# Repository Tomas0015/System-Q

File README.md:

# System-Q
System Q is an open source security system, based on the ESP microcontroller, with wireless and wired bus capabilities.
# I like cheese
We  hate cloud with a passion so there will not be a cloud integration developed by us, the most you will get is a GSM modem sending out SMS messages. 

 # Central control unit
-doesn't actually control anything, only contains a power supply and a battery.

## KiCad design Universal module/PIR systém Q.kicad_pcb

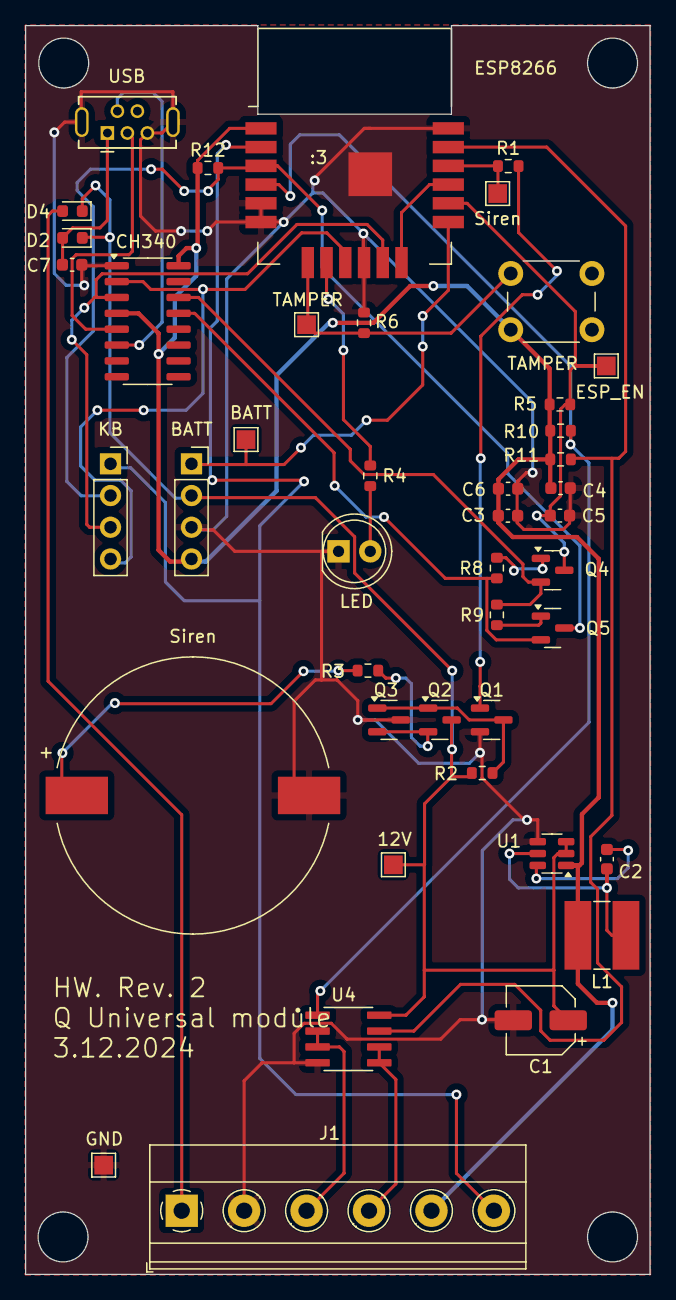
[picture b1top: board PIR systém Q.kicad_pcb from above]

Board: 2 copper layers, 50.0 x 100.0 mm, 43 parts (0 on the bottom side), 32 nets.

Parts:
12V: 12V; TestPoint_Pad_1.5x1.5mm
BATT: Conn_01x04_Socket; PinSocket_1x04_P2.54mm_Vertical
BATT#2: batt test; TestPoint_Pad_1.5x1.5mm
C1: 10u 50V; CP_Elec_5x5.3
C2, C5: 100n; C_0603_1608Metric
C3, C4: 22u; C_0603_1608Metric
C6, C7: 100nF; C_0603_1608Metric
CH340: CH340C; SOIC-16_3.9x9.9mm_P1.27mm
D2, D4: D; D_0603_1608Metric
ESP8266: WT8266-S1
ESP_EN: reset test; TestPoint_Pad_1.5x1.5mm
GND: GND; TestPoint_Pad_1.5x1.5mm
J1: Screw_Terminal_01x06; TerminalBlock_Phoenix_MKDS-1,5-6_1x06_P5.00mm_Horizontal
KB: Conn_01x04_Socket; PinSocket_1x04_P2.54mm_Vertical
L1: 4u7; L_Ferrocore_DLG-0504
LED: LED - R; LED_D5.0mm
Q1, Q2: BC846; SOT-23
Q3: BC857; SOT-23
Q4, Q5: BC817; SOT-23
R1, R2, R8, R9, R10, R11, R12: 10k; R_0603_1608Metric
R3: 820; R_0603_1608Metric
R4: 100R; R_0603_1608Metric
R5: 10K; R_0603_1608Metric
R6: 4k7; R_0603_1608Metric
Siren: buzzer test; TestPoint_Pad_1.5x1.5mm
Siren#2: Siren; LPT2270AS
TAMPER: tamper switch; SW_PUSH_6mm
TAMPER#2: tamper test; TestPoint_Pad_1.5x1.5mm
U1: AP63203WU; TSOT-23-6
U4: P82B96; SOIC127P599X175-8N
USB: USB_B_Mini; USB_Mini-B_Tensility_54-00023_Vertical

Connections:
+3.3V: BATT.4, C3.1, C4.1, C6.1, CH340.4 (V3), CH340.16 (VCC), ESP8266.1 (VCC), J1.5, L1.2, R5.2, R10.1, R11.1, R12.1, TAMPER.1 (A), U1.1 (FB)
+12V: 12V.1, BATT.2, C1.1, D2.1 (K), D4.1 (K), Q2.3 (C), R2.1, U1.2 (EN), U1.3 (IN), U4.8 (VCC)
ESP_EN: C5.1, ESP8266.14 (EN), ESP_EN.1, Q4.3 (C), R5.1
GND: BATT.3, C1.2, C3.2, C4.2, C5.2, C6.2, C7.2, CH340.1 (GND), ESP8266.5 (GPIO15), ESP8266.6 (GND), ESP8266.10 (GND), ESP8266.18 (GND), ESP8266.19, GND.1, J1.2, LED.1 (K), Q1.2 (E), Q3.3 (C), R6.2, Siren#2.2 (+), U1.4 (GND), U4.4 (GND), USB.5 (GND), USB.6 (Shield)
GPIO0: ESP8266.3 (GPIO0), KB.2, Q5.3 (C), R12.2
I2C data: ESP8266.4 (GPIO2), R10.2, U4.1 (SDA)
unnamed: R3.2, Siren#2.1 (-)
unnamed: LED.2 (A), R4.2
unnamed: C7.1, D2.2 (A), USB.1 (VBUS)
unnamed: D4.2 (A), J1.1
unnamed: CH340.5 (UD+), USB.3 (D+)
unnamed: CH340.6 (UD-), USB.2 (D-)
unnamed: Q1.1 (B), R1.2
unnamed: Q1.3 (C), Q2.1 (B), Q3.1 (B), R2.2
unnamed: Q2.2 (E), Q3.2 (E), R3.1
unnamed: Q4.1 (B), R8.2
unnamed: CH340.14 (~RTS), Q4.2 (E), R9.1
unnamed: Q5.1 (B), R9.2
unnamed: CH340.13 (~DTR), Q5.2 (E), R8.1
unnamed: C2.2, U1.6 (BST)
unnamed: C2.1, L1.1, U1.5 (SW)
unnamed: ESP8266.8 (GPIO5), R4.1
unnamed: ESP8266.12 (~RST), ESP8266.15 (GPIO16)
PIR Signal: ESP8266.2 (GPIO4), J1.6, KB.1
RX: CH340.2 (TXD), ESP8266.9 (GPIO3/RXD), KB.4
SCL: J1.4, U4.5 (TXD-SCL), U4.6 (RXD-SCL)
SDA: J1.3, U4.2 (RXD-SDA), U4.3 (TXD-SDA)
TX: CH340.3 (RXD), ESP8266.11 (GPIO1/TXD), KB.3
battery voltage: BATT.1, BATT#2.1, ESP8266.13 (ADC)
buzzer signal: ESP8266.16 (GPIO12), R1.1, Siren.1
clock: ESP8266.17 (GPIO14), R11.2, U4.7 (SCL)
tamper: ESP8266.7 (GPIO13), R6.1, TAMPER.2 (B), TAMPER#2.1

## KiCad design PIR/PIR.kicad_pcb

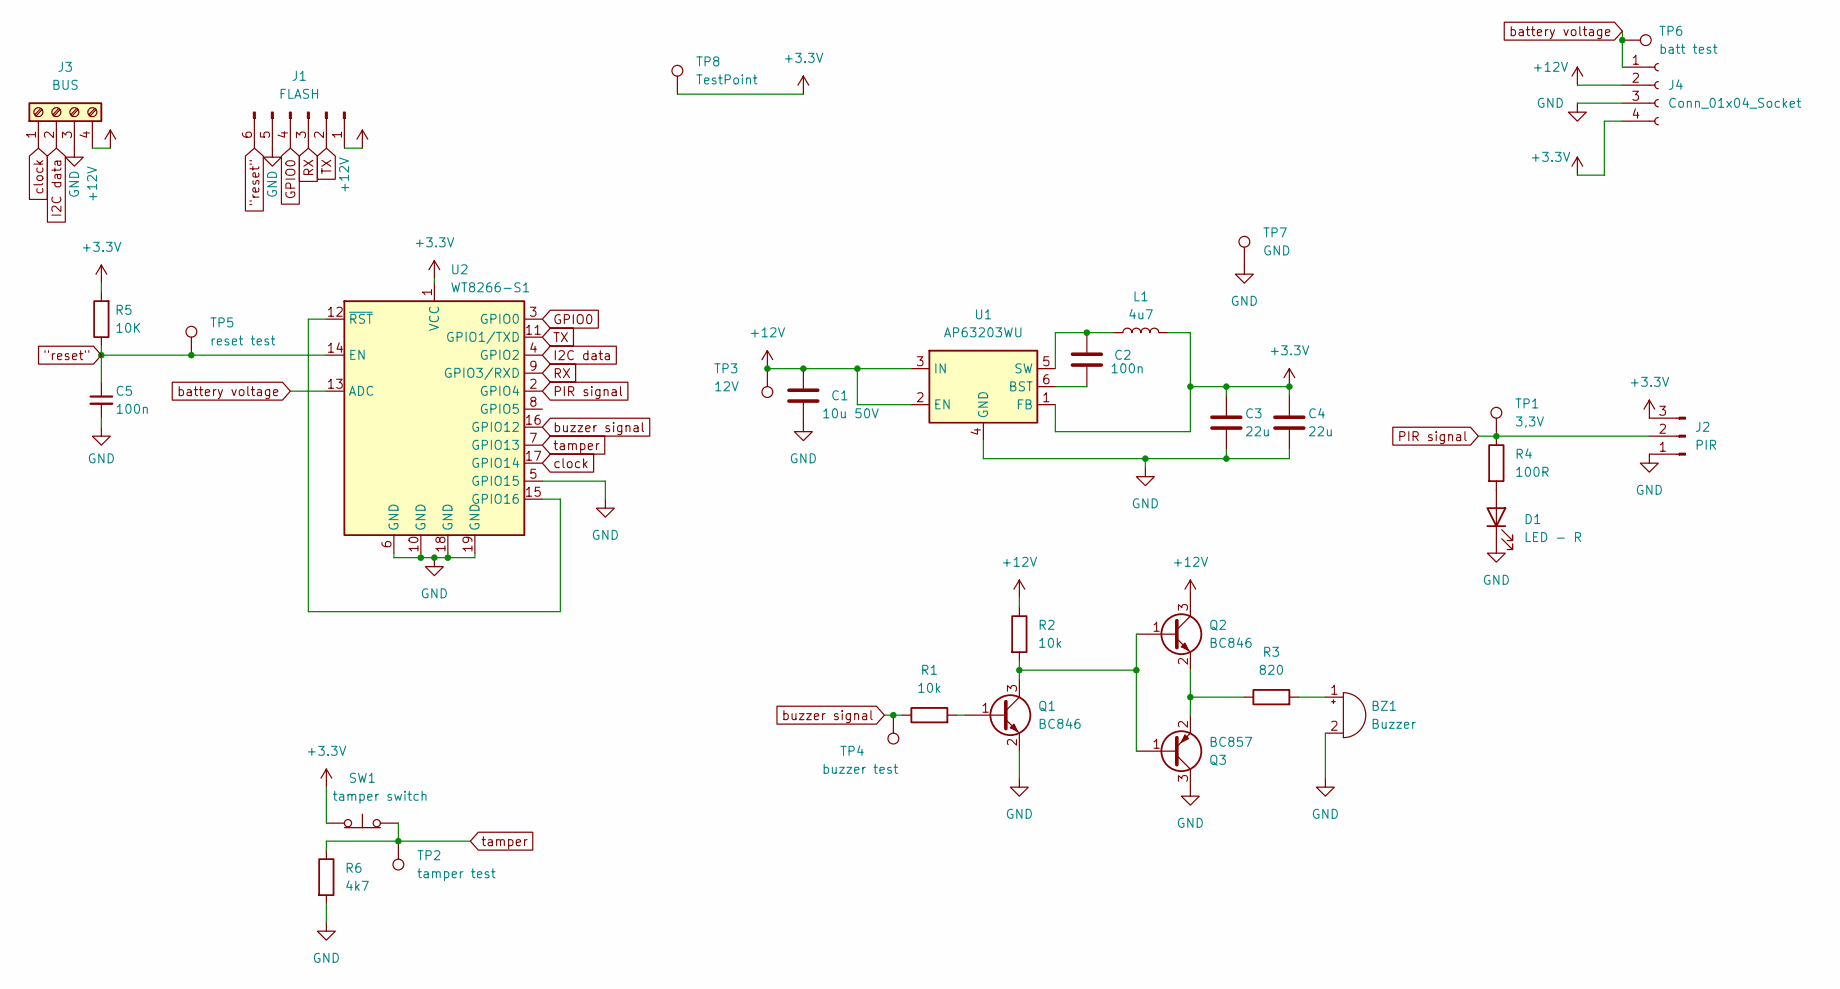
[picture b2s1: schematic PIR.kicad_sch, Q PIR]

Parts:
BZ1: Buzzer; LPT2270AS
C1: 10u 50V; CP_Elec_5x5.3
C2, C5: 100n; C_0603_1608Metric
C3, C4: 22u; C_0603_1608Metric
D1: LED - R; LED_D5.0mm
J1: FLASH; PinSocket_1x06_P2.54mm_Horizontal
J2: PIR; PinSocket_1x03_P2.54mm_Vertical
J3: BUS; TerminalBlock_Altech_AK300-4_P5.00mm
J4: Conn_01x04_Socket; PinSocket_1x04_P2.54mm_Horizontal
L1: 4u7; L_Ferrocore_DLG-0504
Q1, Q2: BC846; SOT-23
Q3: BC857; SOT-23
R1, R2: 10k; R_0603_1608Metric
R3: 820; R_0603_1608Metric
R4: 100R; R_0603_1608Metric
R5: 10K; R_0603_1608Metric
R6: 4k7; R_0603_1608Metric
SW1: tamper switch; SW_PUSH_6mm
TP1: 3,3V; TestPoint_Pad_1.5x1.5mm
TP2: tamper test; TestPoint_Pad_1.5x1.5mm
TP3: 12V; TestPoint_Pad_1.5x1.5mm
TP4: buzzer test; TestPoint_Pad_1.5x1.5mm
TP5: reset test; TestPoint_Pad_1.5x1.5mm
TP6: batt test; TestPoint_Pad_1.5x1.5mm
TP7: GND; TestPoint_Pad_1.5x1.5mm
TP8: TestPoint; TestPoint_Pad_1.5x1.5mm
U1: AP63203WU; TSOT-23-6
U2: WT8266-S1

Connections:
"reset": C5.1, J1.6, R5.1, TP5.1, U2.14 (EN)
+3.3V: C3.1, C4.1, J2.3, J4.4, L1.2, R5.2, SW1.1 (A), TP8.1, U1.1 (FB), U2.1 (VCC)
+12V: C1.1, J1.1, J3.4, J4.2, Q2.3 (C), R2.1, TP3.1, U1.2 (EN), U1.3 (IN)
GND: BZ1.2 (+), C1.2, C3.2, C4.2, C5.2, D1.1 (K), J1.5, J2.1, J3.3, J4.3, Q1.2 (E), Q3.3 (C), R6.2, TP7.1, U1.4 (GND), U2.5 (GPIO15), U2.6 (GND), U2.10 (GND), U2.18 (GND), U2.19 (GND)
GPIO0: J1.4, U2.3 (GPIO0)
I2C data: J3.2, U2.4 (GPIO2)
unnamed: BZ1.1 (-), R3.2
unnamed: D1.2 (A), R4.2
unnamed: Q1.1 (B), R1.2
unnamed: Q1.3 (C), Q2.1 (B), Q3.1 (B), R2.2
unnamed: Q2.2 (E), Q3.2 (E), R3.1
unnamed: C2.1, U1.6 (BST)
unnamed: C2.2, L1.1, U1.5 (SW)
unnamed: U2.12 (~RST), U2.15 (GPIO16)
PIR signal: J2.2, R4.1, TP1.1, U2.2 (GPIO4)
RX: J1.3, U2.9 (GPIO3/RXD)
TX: J1.2, U2.11 (GPIO1/TXD)
battery voltage: J4.1, TP6.1, U2.13 (ADC)
buzzer signal: R1.1, TP4.1, U2.16 (GPIO12)
clock: J3.1, U2.17 (GPIO14)
tamper: R6.1, SW1.2 (B), TP2.1, U2.7 (GPIO13)

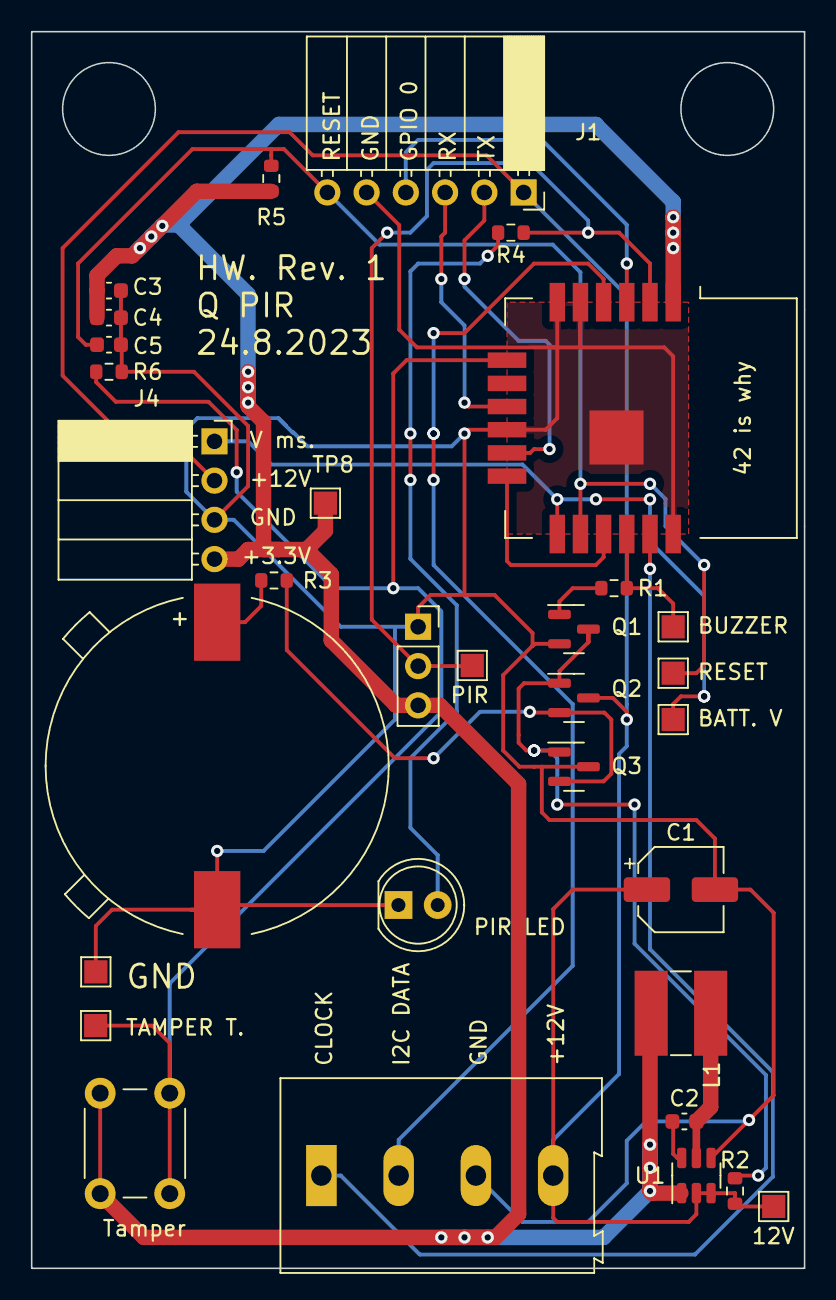
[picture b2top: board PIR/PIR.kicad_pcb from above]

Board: 2 copper layers, 50.0 x 80.0 mm, 32 parts (0 on the bottom side), 21 nets.

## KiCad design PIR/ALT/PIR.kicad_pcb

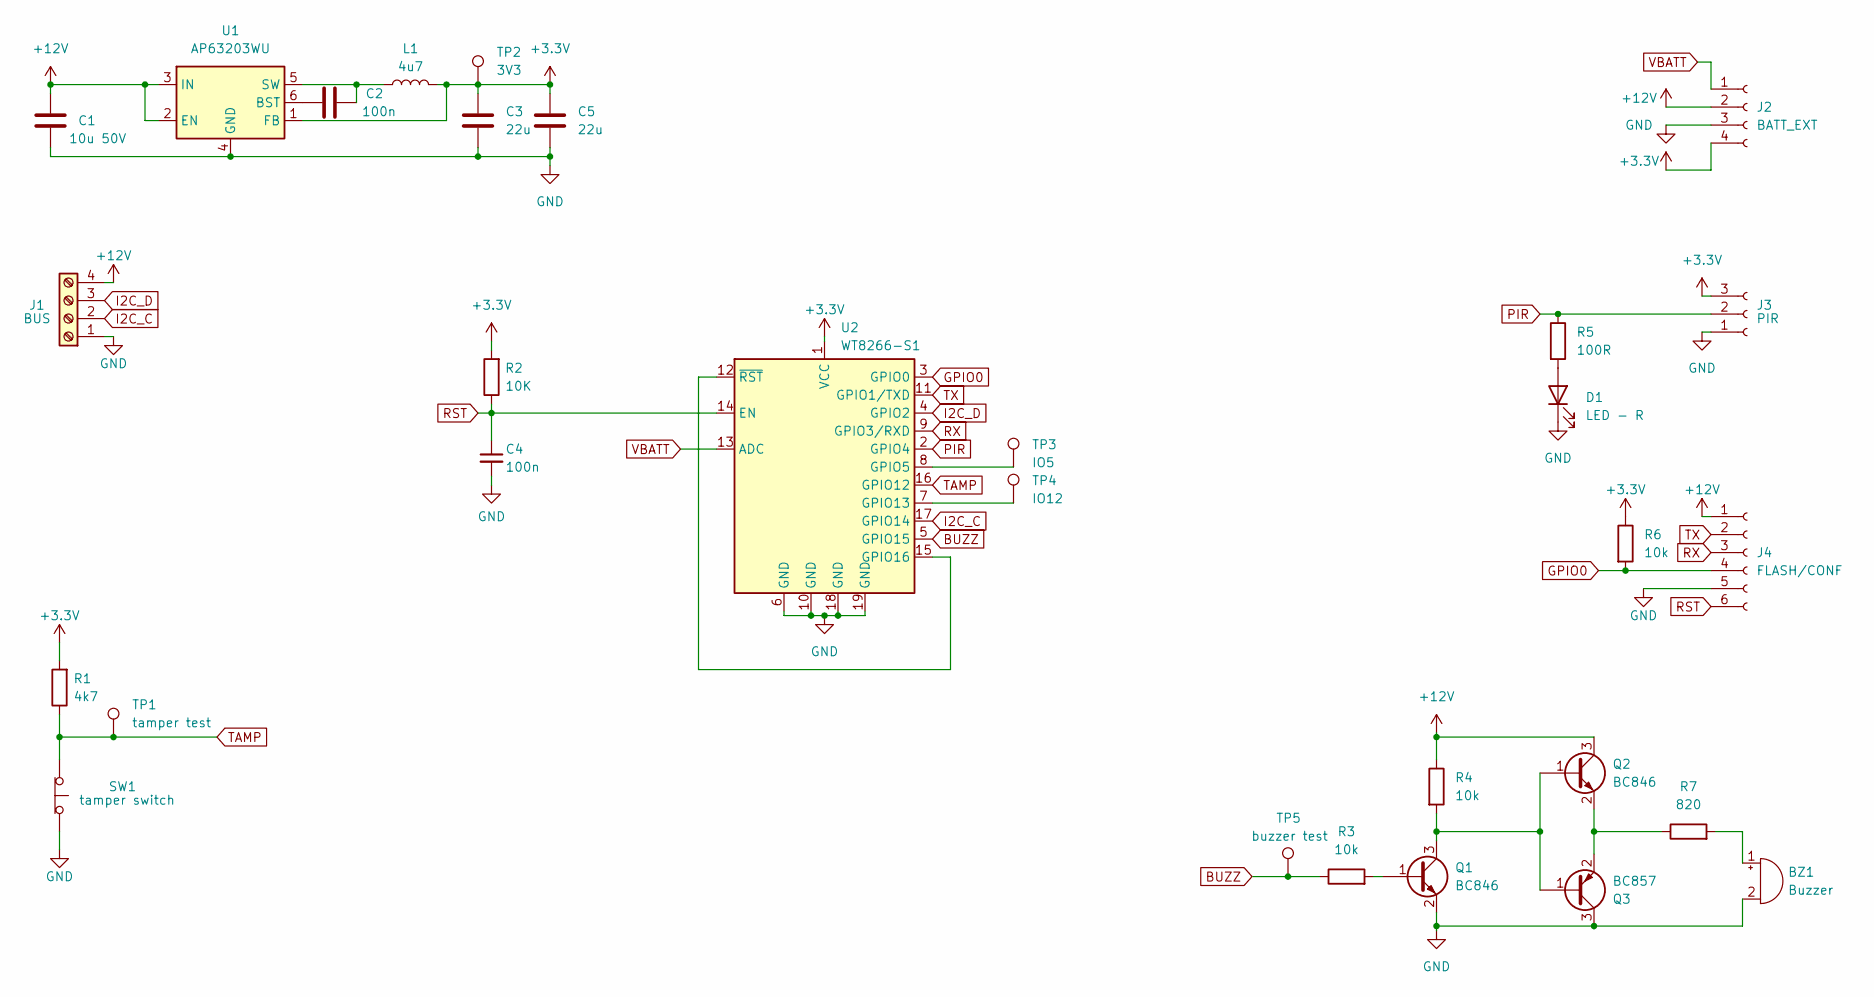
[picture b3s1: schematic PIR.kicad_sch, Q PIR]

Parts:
BZ1: Buzzer; LPT2270AS
C1: 10u 50V; CP_Elec_5x5.3
C2, C4: 100n; C_0603_1608Metric
C3, C5: 22u; C_0603_1608Metric
D1: LED - R; LED_D5.0mm
J1: BUS; TerminalBlock_Altech_AK300-4_P5.00mm
J2: BATT_EXT; PinSocket_1x04_P2.54mm_Horizontal
J3: PIR; PinHeader_1x03_P2.54mm_Vertical
J4: FLASH/CONF; PinSocket_1x06_P2.54mm_Horizontal
L1: 4u7; L_Ferrocore_DLG-0504
Q1, Q2: BC846; SOT-23
Q3: BC857; SOT-23
R1: 4k7; R_0603_1608Metric
R2: 10K; R_0603_1608Metric
R3, R4, R6: 10k; R_0603_1608Metric
R5: 100R; R_0603_1608Metric
R7: 820; R_0603_1608Metric
SW1: tamper switch; SW_PUSH_6mm
TP1: tamper test; TestPoint_Pad_1.5x1.5mm
TP2: 3V3; TestPoint_Pad_1.5x1.5mm
TP3: IO5; TestPoint_Pad_1.5x1.5mm
TP4: IO12; TestPoint_Pad_1.5x1.5mm
TP5: buzzer test; TestPoint_Pad_1.5x1.5mm
U1: AP63203WU; TSOT-23-6
U2: WT8266-S1

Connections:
+3.3V: C3.1, C5.1, J2.4, J3.3, L1.2, R1.2, R2.2, R6.1, TP2.1, U1.1 (FB), U2.1 (VCC)
+12V: C1.1, J1.4, J2.2, J4.1, Q2.3 (C), R4.1, U1.2 (EN), U1.3 (IN)
BUZZ: R3.1, TP5.1, U2.5 (GPIO15)
GND: BZ1.2 (+), C1.2, C3.2, C4.2, C5.2, D1.1 (K), J1.1, J2.3, J3.1, J4.5, Q1.2 (E), Q3.3 (C), SW1.2 (B), U1.4 (GND), U2.6 (GND), U2.10 (GND), U2.18 (GND), U2.19 (GND)
GPIO0: J4.4, R6.2, U2.3 (GPIO0)
I2C_C: J1.2, U2.17 (GPIO14)
I2C_D: J1.3, U2.4 (GPIO2)
unnamed: BZ1.1 (-), R7.2
unnamed: D1.2 (A), R5.2
unnamed: Q1.1 (B), R3.2
unnamed: Q1.3 (C), Q2.1 (B), Q3.1 (B), R4.2
unnamed: Q2.2 (E), Q3.2 (E), R7.1
unnamed: C2.1, U1.6 (BST)
unnamed: C2.2, L1.1, U1.5 (SW)
unnamed: TP3.1, U2.8 (GPIO5)
unnamed: TP4.1, U2.7 (GPIO13)
unnamed: U2.12 (~RST), U2.15 (GPIO16)
PIR: J3.2, R5.1, U2.2 (GPIO4)
RST: C4.1, J4.6, R2.1, U2.14 (EN)
RX: J4.3, U2.9 (GPIO3/RXD)
TAMP: R1.1, SW1.1 (A), TP1.1, U2.16 (GPIO12)
TX: J4.2, U2.11 (GPIO1/TXD)
VBATT: J2.1, U2.13 (ADC)

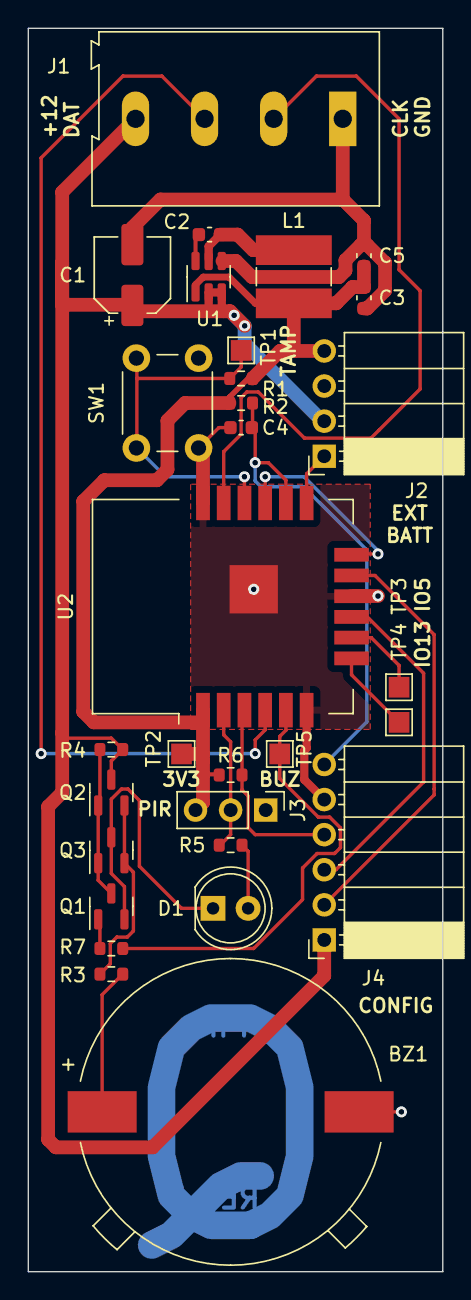
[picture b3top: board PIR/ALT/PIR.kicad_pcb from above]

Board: 2 copper layers, 30.0 x 90.0 mm, 30 parts (0 on the bottom side), 23 nets.

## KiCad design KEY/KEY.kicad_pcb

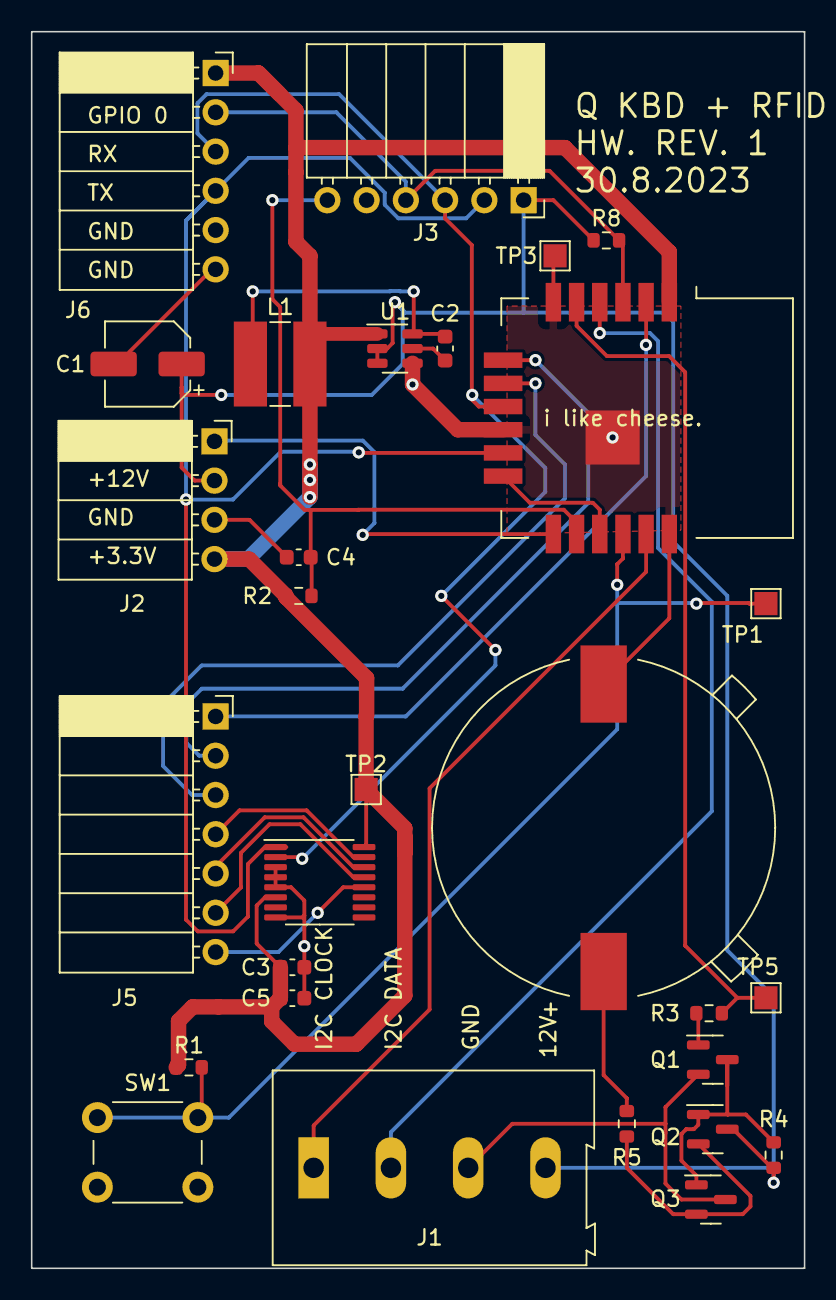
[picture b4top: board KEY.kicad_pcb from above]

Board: 2 copper layers, 50.0 x 80.0 mm, 29 parts (0 on the bottom side), 26 nets.

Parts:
BZ1: Buzzer; LPT2270AS
C1: 10u 50V; CP_Elec_5x5.3
C2, C4: 100n; C_0603_1608Metric
C3, C5: 22u; C_0603_1608Metric
J1: BUS; TerminalBlock_Altech_AK300-4_P5.00mm
J2: BATT_EXT; PinSocket_1x04_P2.54mm_Horizontal
J3: FLASH/CONF; PinSocket_1x06_P2.54mm_Horizontal
J5: KEYB; PinSocket_1x07_P2.54mm_Horizontal
J6: RFID; PinSocket_1x06_P2.54mm_Horizontal
L1: 4u7; L_Ferrocore_DLG-0504
Q1, Q2: BC846; SOT-23
Q3: BC857; SOT-23
R1, R2, R8: 10K; R_0603_1608Metric
R3, R4: 10k; R_0603_1608Metric
R5: 820; R_0603_1608Metric
SW1: tamper switch; SW_PUSH_6mm
TP1: tamper test; TestPoint_Pad_1.5x1.5mm
TP2: 3V3; TestPoint_Pad_1.5x1.5mm
TP3: TestPoint; TestPoint_Pad_1.5x1.5mm
TP5: buzzer test; TestPoint_Pad_1.5x1.5mm
U1: AP63203WU; TSOT-23-6
U2: WT8266-S1
U3: 74LVC138; TSSOP-16_4.4x5mm_P0.65mm

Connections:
+3.3V: C3.1, C5.1, J2.4, J6.1, L1.2, R1.1, R2.2, TP2.1, U1.1 (FB), U2.1 (VCC), U3.6 (E3), U3.16 (VCC)
+12V: C1.1, J1.4, J2.2, J3.1, Q2.3 (C), R4.1, R8.1, U1.2 (EN), U1.3 (IN)
BUZZ: R3.1, TP5.1, U2.5 (GPIO15)
GND: BZ1.2 (+), C1.2, C3.2, C4.2, C5.2, J1.3, J2.3, J3.5, J6.5, J6.6, Q1.2 (E), Q3.3 (C), SW1.2 (B), TP3.1, U1.4 (GND), U2.6 (GND), U2.10 (GND), U2.18 (GND), U2.19 (GND), U3.3 (A2), U3.4 (E1), U3.5 (E2), U3.8 (GND)
GPIO0: J3.4, J6.2, R8.2, U2.3 (GPIO0)
I2C_C: J1.1, U2.17 (GPIO14)
I2C_D: J1.2, U2.4 (GPIO2)
unnamed: BZ1.1 (-), R5.2
unnamed: J5.4, U3.15 (O0)
unnamed: J5.5, U3.14 (O1)
unnamed: J5.6, U3.13 (O2)
unnamed: J5.7, U3.12 (O3)
unnamed: Q1.1 (B), R3.2
unnamed: Q1.3 (C), Q2.1 (B), Q3.1 (B), R4.2
unnamed: Q2.2 (E), Q3.2 (E), R5.1
unnamed: C2.2, L1.1, U1.6 (BST)
unnamed: C2.1, U1.5 (SW)
unnamed: U2.12 (~RST), U2.15 (GPIO16)
RST: C4.1, J3.6, R2.1, U2.14 (EN)
RX: J3.3, J6.3, U2.9 (GPIO3/RXD), U3.2 (A1)
TAMP: R1.2, SW1.1 (A), TP1.1, U2.16 (GPIO12)
TX: J3.2, J6.4, U2.11 (GPIO1/TXD), U3.1 (A0)
VBATT: J2.1, U2.13 (ADC)
Y0: J5.1, U2.2 (GPIO4)
Y1: J5.2, U2.7 (GPIO13)
Y2: J5.3, U2.8 (GPIO5)

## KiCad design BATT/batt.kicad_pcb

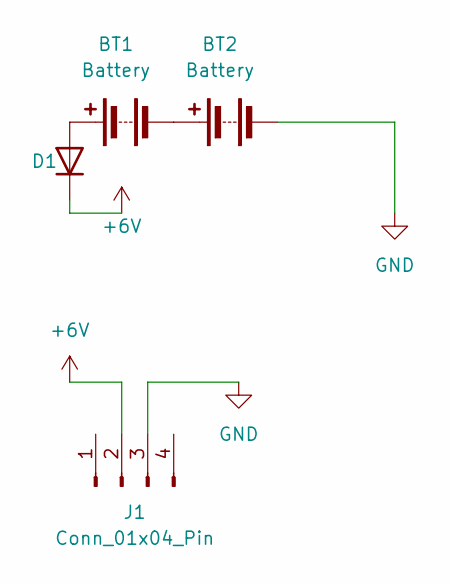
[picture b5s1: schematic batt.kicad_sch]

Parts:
BT1, BT2: Battery; BatteryHolder_Keystone_2468_2xAAA
D1: D; D_A-405_P10.16mm_Horizontal
J1: Conn_01x04_Pin; PinHeader_1x04_P2.54mm_Vertical

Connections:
+6V: D1.1 (K), J1.2
GND: BT2.2 (-), J1.3
unnamed: BT1.1 (+), D1.2 (A)
unnamed: BT1.2 (-), BT2.1 (+)

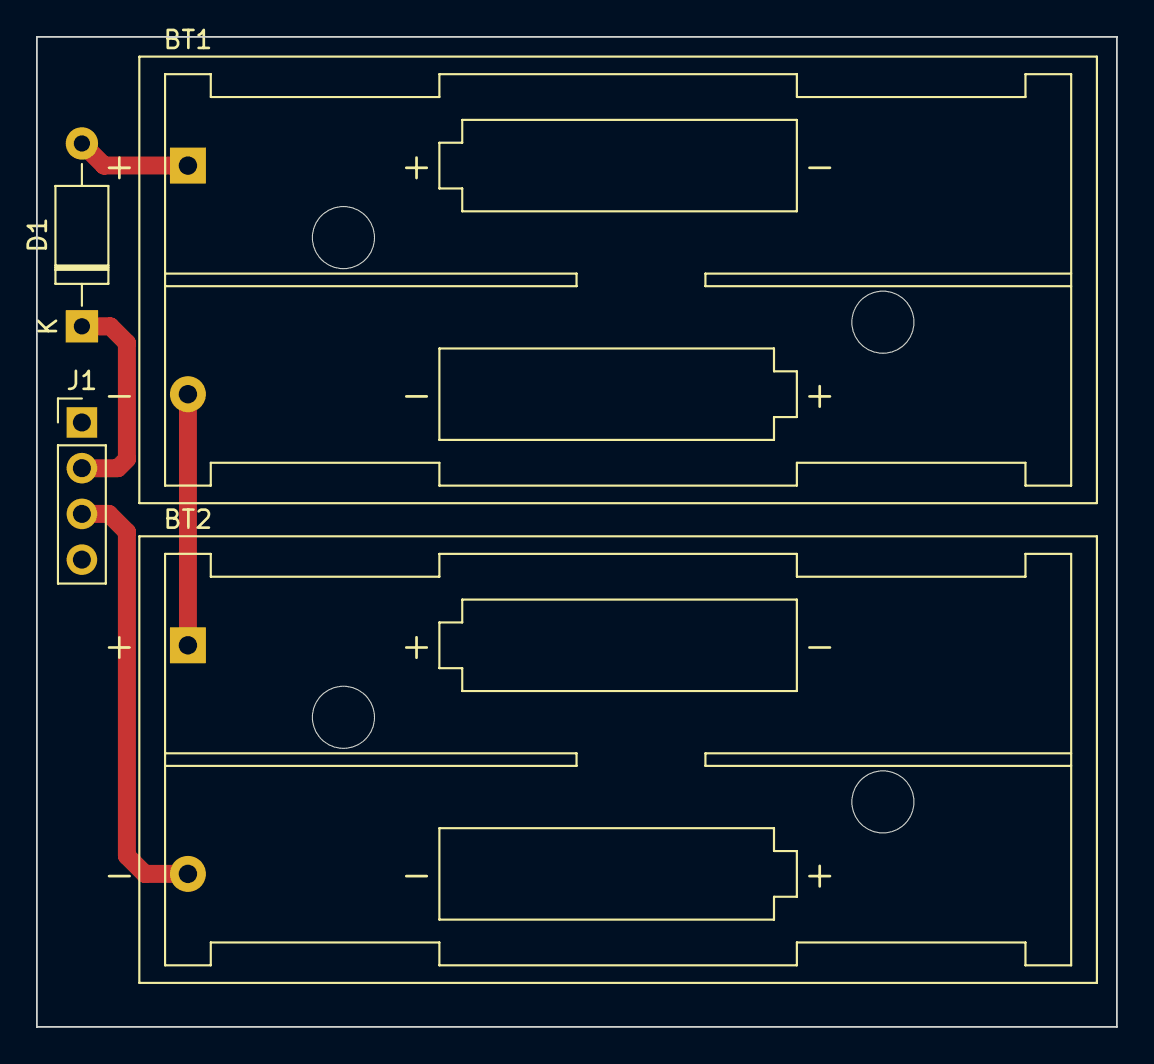
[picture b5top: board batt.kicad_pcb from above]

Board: 2 copper layers, 60.0 x 55.0 mm, 4 parts (0 on the bottom side), 4 nets.

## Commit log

2023-08-30 initail commit
2023-08-30 Add pcb design
2023-08-30 Wires are cool
2023-08-30 Enhance PCB design
2023-09-03 Create cheese
2023-09-03 Add files via upload
    first version of the schematic for the backup battery
2023-09-03 Update README.md
    doom
2023-09-03 Update README.md
    problem description
2023-09-07 Fixed typo
2023-09-07 upgrades people, upgrades!
2023-09-07 Removed Hardwario
2023-09-21 Update WT8266 datasheet
2023-09-21 Add ground pad to WT8266
2023-09-21 Update symbol and footprint of WT8266
2023-09-21 Fix incident
2024-10-30 Add files via upload
    better PCB design
2024-10-30 Create Universal module
2024-10-30 create og universal module design
2024-10-31 better diode
2024-11-16 add features
2024-11-17 better design
2024-11-24 begun the drawing of the PCB, fixed libraries
2024-12-01 basic PCB design
2024-12-03 finish PCB design, bonus gerber files
2024-12-03 fix small issues
